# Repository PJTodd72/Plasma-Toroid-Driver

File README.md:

# Plasma-Toroid-Driver

Version one of the Ki-Cad schematics and PCB layout of the Plasma Toroid generator driver circuits.

Also included are the Gerber files and interactive BOM generated by Ki-Cad.

Included is a simulation in LT spice of the driver circuit with no load.
This circuit oscillates as expected, however a simulation of the plasma load needs to be added for completion.

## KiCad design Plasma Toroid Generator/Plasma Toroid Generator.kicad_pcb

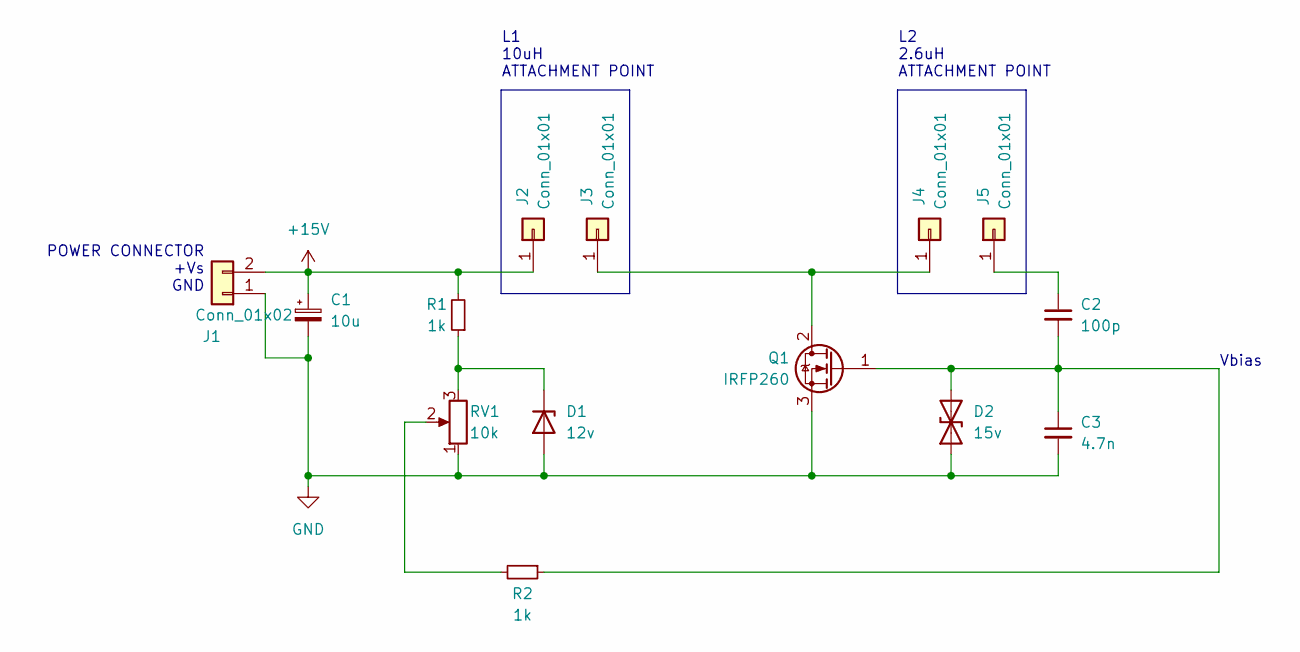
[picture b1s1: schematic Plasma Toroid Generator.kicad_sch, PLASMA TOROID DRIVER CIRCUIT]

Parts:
C1: 10u; CP_Radial_D10.0mm_P5.00mm
C2: 100p; C_Rect_L18.0mm_W5.0mm_P15.00mm_FKS3_FKP3
C3: 4.7n; C_Rect_L7.2mm_W2.5mm_P5.00mm_FKS2_FKP2_MKS2_MKP2
D1: 12v; D_DO-41_SOD81_P10.16mm_Horizontal
D2: 15v; D_DO-27_P15.24mm_Horizontal
J1: Conn_01x02; TerminalBlock_Phoenix_PT-1,5-2-5.0-H_1x02_P5.00mm_Horizontal
J2, J3, J4, J5: Conn_01x01; PinSocket_1x01_P2.54mm_Vertical
Q1: IRFP260; TO-247-3_Vertical
R1, R2: 1k; R_Axial_DIN0414_L11.9mm_D4.5mm_P15.24mm_Horizontal
RV1: 10k; Bourns PDB12-H

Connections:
+15V: C1.1, J1.2, J2.1, R1.2
GND: C1.2, C3.2, D1.2 (A), D2.1 (A1), J1.1, Q1.3 (S), RV1.1
unnamed: C2.1, J5.1
unnamed: C2.2, C3.1, D2.2 (A2), Q1.1 (G), R2.1
unnamed: D1.1 (K), R1.1, RV1.3
unnamed: J3.1, J4.1, Q1.2 (D)
unnamed: R2.2, RV1.2

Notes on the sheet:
POWER CONNECTOR +Vs GND
L1 10uH ATTACHMENT POINT
L2 2.6uH ATTACHMENT POINT
Vbias

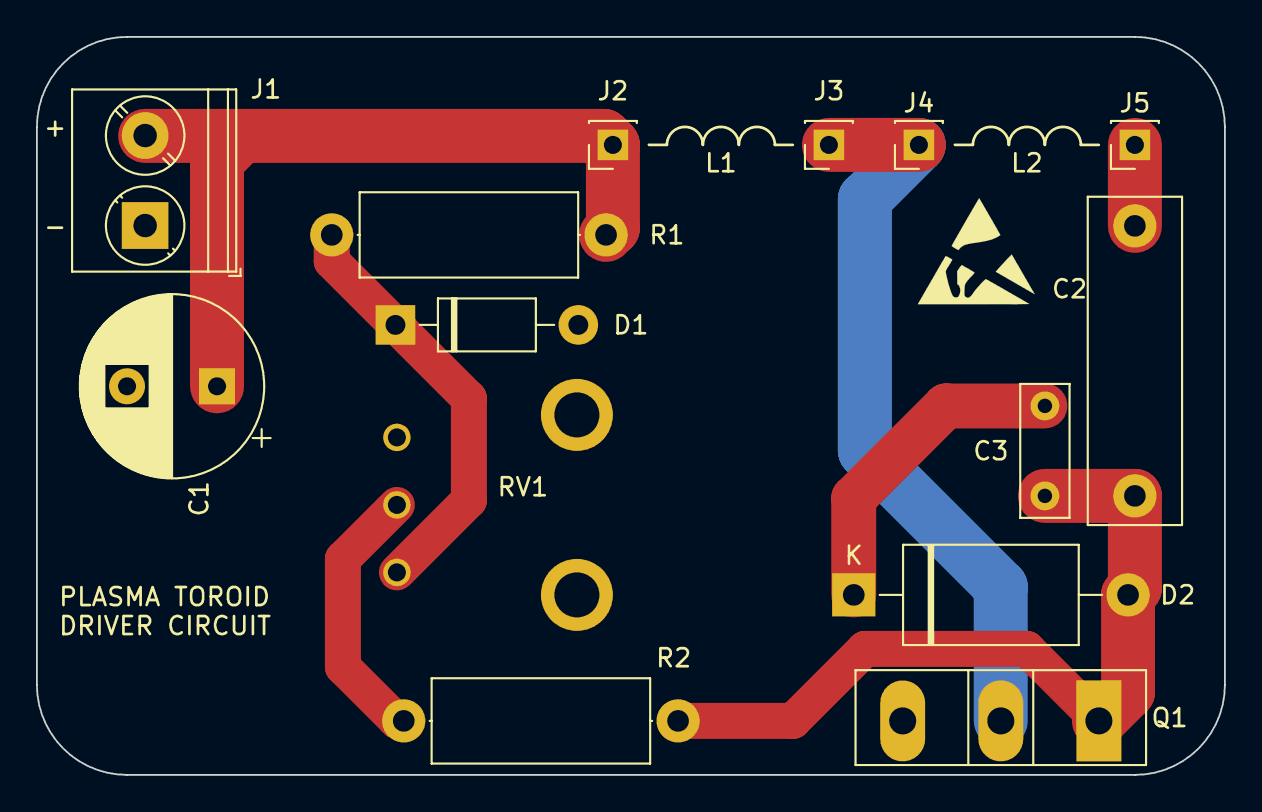
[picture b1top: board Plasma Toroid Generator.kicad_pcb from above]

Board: 2 copper layers, 66.0 x 41.0 mm, 14 parts (0 on the bottom side), 7 nets.

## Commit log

2023-01-12 Version one of the schematics
2023-01-12 Added list of components as sourced from DigiKey
2023-01-12 Added LTSpice file that doesn't work as of yet
2023-01-26 Working simulation of the oscillating circuit
2023-01-29 Tested changing the oscillation frequency of the circuit
2023-02-06 Updated PCB layout to fix errors in cap placement
2023-03-13 Updates to model to accurately reflect the physical circuit
